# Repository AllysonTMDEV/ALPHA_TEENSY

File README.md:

# AFC - Alpha Flight Controller (Teensy 4.1)

## Visao Geral

Controlador de navegacao desenvolvido pela **Alpha Subsea** para ROVs e drones subaquaticos, baseado na plataforma **Teensy 4.1** (ARM Cortex-M7 @ 600MHz).

### Caracteristicas Principais:
- **MCU:** Teensy 4.1 (600MHz, 1MB RAM)
- **Sensores:** IMU (ICM-42688-P), Magnetometro (LIS3MDL), Barometro (BMP390), Profundidade (MS5837-30BA)
- **PWM:** 16 canais via PCA9685 (8 thrusters + 4 servos)
- **Comunicacao:** Serial 1Mbps com Raspberry Pi
- **ADC:** ADS1115 16-bit para monitoramento de tensao/corrente

## Estrutura de Arquivos

```
AFC_CICLO DESENVOLVIMENTO.html    # Ciclo de desenvolvimento (40% completo)
AFC_TEENSY_PCB_DOCUMENTACAO.md    # Documentacao tecnica completa
BOM_AFC_TEENSY_LCSC.csv           # Lista de materiais com codigos LCSC
Gerber_*.zip                       # Arquivos Gerber para fabricacao
PCB_*.json                         # PCB EasyEDA
PCB_*.kicad_pcb                    # PCB KiCad
SCH_*.json                         # Esquematico EasyEDA
Schematic_*.pdf                    # Esquematico PDF
Sheet_1_*.schdoc                   # Esquematico Altium (para KiCad)
*.png                              # Screenshots de validacao
```

## Status do Projeto

| Fase | Progresso | Status |
|------|-----------|--------|
| 1. Plan | 100% | Concluido |
| 2. Code | 100% | Firmware + Esquematico prontos |
| 3. Build | 100% | Gerbers prontos para fabricacao |
| 4. Test | 0% | Pendente |
| 5. Homologation | 0% | Pendente |

**Progresso Geral: 42%**

## BOM - Lista de Materiais

Total de **63 componentes** com codigos LCSC para montagem SMD.

### Componentes Principais:
| Componente | Modelo | LCSC |
|------------|--------|------|
| IMU 6-DoF | ICM-42688-P | C1850418 |
| Magnetometro | LIS3MDL | C478483 |
| Barometro | BMP390 | C9900016584 |
| PWM Driver | PCA9685PW | C2678753 |
| ADC 16-bit | ADS1115 | C37593 |
| Buck Converter | MP1584EN | C15051 |
| Power Monitor | INA226 | C49851 |

**Custo estimado:** ~$50-70 USD (sem Teensy e MS5837)

## Como Fabricar

1. **Fabricacao da PCB:**
   - Utilizar o arquivo `Gerber_*.zip` para fabricacao
   - BOM disponivel em `BOM_AFC_TEENSY_LCSC.csv`

2. **Importar no KiCad 9.0:**
   - `File` -> `Import Project...` -> `Altium Designer`
   - Selecionar `Sheet_1_*.schdoc`

## Firmware

Firmware desenvolvido em PlatformIO com as seguintes features:
- Loop de controle a 400Hz
- PID com anti-windup
- Mixer para 8 thrusters (BlueROV2 Heavy)
- Protocolo binario com CRC16
- Telemetria a 50Hz

## Documentacao

- [Documentacao Tecnica](AFC_TEENSY_PCB_DOCUMENTACAO.md)
- [Ciclo de Desenvolvimento](AFC_CICLO%20DESENVOLVIMENTO.html)
- [BOM LCSC](BOM_AFC_TEENSY_LCSC.csv)

## Equipe

**Alpha Subsea** - Tecnologia Submarina  
Desenvolvido por **Arbor Gestao**

---

*Ultima atualizacao: Janeiro 2026*

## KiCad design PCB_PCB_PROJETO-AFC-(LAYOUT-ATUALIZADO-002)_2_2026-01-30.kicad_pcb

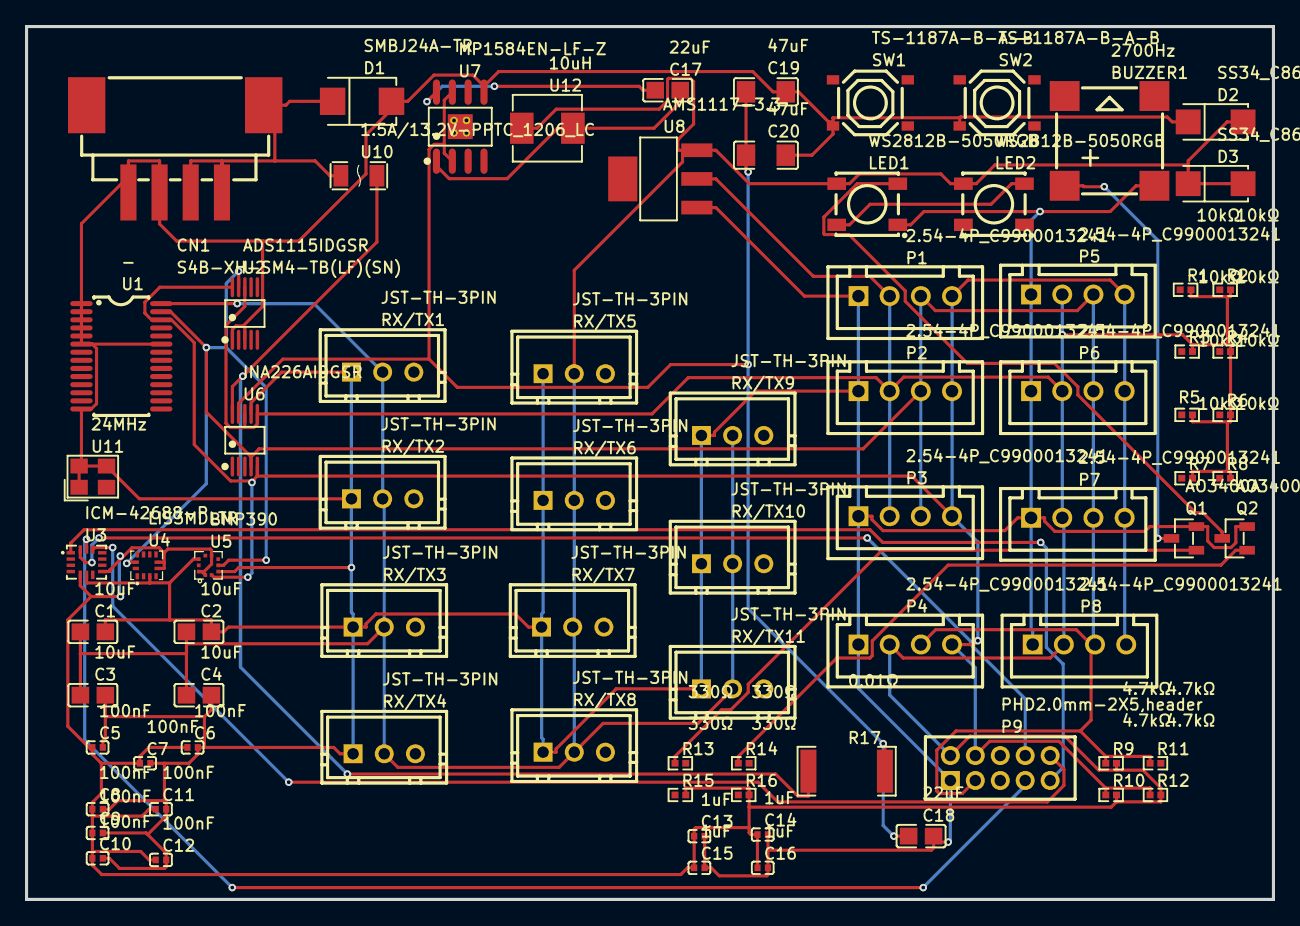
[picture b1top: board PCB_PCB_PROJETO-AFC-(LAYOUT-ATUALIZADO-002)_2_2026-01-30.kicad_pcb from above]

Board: 2 copper layers, 100.0 x 70.0 mm, 79 parts (0 on the bottom side), 19 nets.

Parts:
BUZZER1: 2700Hz; BUZ-SMD_4P-L8.5-W8.5-P8.50-BR
C1, C2, C3, C4: 10uF; C0805
C5, C6, C7, C8, C9, C10, C11, C12: 100nF; C0402
C13, C14, C15, C16: 1uF; C0402
C17, C18: 22uF; C0805
C19, C20: 47uF; C1206
CN1: S4B-XH-SM4-TB(LF)(SN); CONN-SMD_S4B-XH-SM4-TB-LF-SN
D1: SMBJ24A-TR; SMB_L4.6-W3.6-LS5.3-RD
D2, D3: SS34_C8678; SMA_L4.3-W2.6-LS5.2-RD
LED1, LED2: WS2812B-5050RGB; LED-SMD_4P-L5.0-W5.0-BR_WS2812B-5050RGB
P1, P2, P3, P4, P5, P6, P7, P8: 2.54-4P_C9900013241; CONN-TH_B4B-XH-A-BK-LF-SN
P9: PHD2.0mm-2X5,header; CONN-TH_10P-P2.00_PHD2.0MM-2X5
Q1, Q2: AO3400A; SOT-23-3_L2.9-W1.3-P1.90-LS2.4-BR
R1, R2, R3, R4, R5, R6, R7, R8: 10kΩ; R0402
R9, R10, R11, R12: 4.7kΩ; R0402
R13, R14, R15, R16: 330Ω; R0402
R17: 0.01Ω; R2512
RX/TX1, RX/TX2, RX/TX3, RX/TX4, RX/TX5, RX/TX6, RX/TX7, RX/TX8, RX/TX9, RX/TX10, RX/TX11: JST-TH-3PIN; CONN-TH_3P-P2.50_B3B-XH-A-BK-LF-SN
SW1, SW2: TS-1187A-B-A-B; SW-SMD_4P-L5.1-W5.1-P3.70-LS6.5-TL_H1.5
U1: -; TSSOP-28_L9.7-W4.4-P0.65-LS6.4-TL
U2: ADS1115IDGSR; MSOP-10_L3.0-W3.0-P0.50-LS5.0-BL
U3: ICM-42688-P; LGA-14_L3.0-W2.5-P0.50-TL
U4: LIS3MDLTR; LGA-12_L2.0-W2.0-P0.50-BL
U5: BMP390; LGA-10_L2.0-W2.0-P0.50-BL
U6: INA226AIDGSR; MSOP-10_L3.0-W3.0-P0.50-LS5.0-BL
U7: MP1584EN-LF-Z; SOIC-8_L5.0-W4.0-P1.27-LS6.0-BL-EP2.0
U8: AMS1117-3.3; SOT-223-3_L6.5-W3.4-P2.30-LS7.0-BR
U10: 1.5A/13.2V-PPTC_1206_LC; F1206
U11: 24MHz; CRYSTAL-SMD_4P-L3.2-W2.5-BL
U12: 10uH; IND-SMD_L5.4-W5.2

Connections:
3V3: C5.1, C6.1, C7.1, C8.1, C9.1, C10.1, C11.1, C12.1, C13.1, C14.1, C15.1, C16.1, P1.2, P2.2, P3.2, P4.2, P5.2, P6.2, P7.2, P8.2, P9.2, R1.2, R2.2, R3.2, R4.2, R5.2, R6.2, R7.2, R8.2, R9.2, R10.2, R12.2, R15.2, R16.2, U2.8, U3.5, U3.8, U4.5, U4.6, U5.1, U5.6, U5.10, U6.6, U6.8, U8.2
5V: C1.1, C2.1, C3.1, C4.1, D2.2, D3.1, D3.2, LED1.3, LED2.3, RX/TX1.2, RX/TX2.2, RX/TX3.2, RX/TX4.2, RX/TX5.2, RX/TX6.2, RX/TX7.2, RX/TX8.2, RX/TX9.2, RX/TX10.2, RX/TX11.2, U1.28, U8.3, U12.2
BUZZER: BUZZER1.1, Q1.3
BUZZER_CTRL: Q1.1, R13.1
CN1_1: CN1.1, CN1.2, CN1.6, D1.1, U10.1
GND: BUZZER1.2, C1.2, C2.2, C3.2, C4.2, C5.2, C6.2, C7.2, C8.2, C9.2, C10.2, C11.2, C12.2, C13.2, C14.2, C15.2, C16.2, C18.2, C19.2, C20.2, CN1.3, CN1.4, D1.2, D2.1, LED1.1, P1.1, P2.1, P3.1, P4.1, P5.1, P6.1, P7.1, P8.1, P9.1, Q1.2, Q2.2, RX/TX1.1, RX/TX2.1, RX/TX3.1, RX/TX4.1, RX/TX5.1, RX/TX6.1, RX/TX7.1, RX/TX8.1, RX/TX9.1, RX/TX10.1, RX/TX11.1, SW1.3, SW2.3, U1.1, U1.2, U1.3, U1.4, U1.5, U1.6, U1.14, U1.23, U2.1, U2.3, U3.6, U4.3, U5.3, U5.8, U6.7, U7.5, U8.1, U11.1, U11.3, U11.4
IMU_CS: P9.10, U3.12
LED1_4: LED1.4, LED2.2
LED_CTRL: Q2.1, R14.1
LED_DATA: LED1.2, Q2.3
R17_2: C18.1, C19.1, C20.1, R17.2, U6.9, U7.2, U7.7
SCL: P1.4, P2.4, P3.4, P4.4, P5.4, P6.4, P7.4, P8.4, P9.4, R10.1, R12.1, U1.26, U2.10, U5.2, U6.5
SDA: P1.3, P2.3, P3.3, P4.3, P5.3, P6.3, P7.3, P8.3, P9.3, R9.1, R11.1, U1.27, U2.9, U4.11, U5.4, U6.4
SPI_CLK: P9.7, U3.13
SPI_MISO: P9.9, U3.1
SPI_MOSI: P9.8, U3.14
U7_1: C17.2, U7.1, U12.1
U7_8: C17.1, U7.8
U10_2: R17.1, U6.10, U10.2

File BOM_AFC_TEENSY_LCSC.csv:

Referencia,Quantidade,Valor/Part Number,Descricao,Footprint,LCSC,Tipo JLCPCB
========== ICs PRINCIPAIS ==========
U1,1,PCA9685PW 118,PWM Driver 16ch I2C,TSSOP-28,C2678753,Extended Part
U2,1,ADS1115IDGSR,ADC 16-bit 4ch I2C,MSOP-10,C37593,Extended Part
U3,1,ICM-42688-P,IMU 6-axis Accel/Gyro,LGA-14,C1850418,Extended Part
U4,1,LIS3MDLTR,Magnetometro 3-axis I2C,LGA-12,C478483,Extended Part
U5,1,BMP390,Barometro/Altimetro I2C,LGA-10,C9900016584,Extended Part
U6,1,INA226AIDGSR,Monitor Corrente/Tensao I2C,MSOP-10,C49851,Extended Part
U7,1,MP1584EN-LF-Z,Buck Converter 3A,SOIC-8 EP,C15051,Extended Part
U8,1,AMS1117-3.3,LDO Regulador 3.3V 1A,SOT-223,C6186,Basic Part
U10,1,PPTC 1.5A/13.2V,Fusivel Resetavel,1206,C9900007450,Extended Part
U11,1,7325-2400A1210-03,Crystal 24MHz,SMD 3225,C17701336,Extended Part
========== DIODOS ==========
D1,1,SMBJ24A-TR,TVS Diodo 24V,SMB,C133668,Extended Part
D2,1,SS34,Schottky Diodo 3A 40V,SMA,C8678,Basic Part
D3,1,SS34,Schottky Diodo 3A 40V,SMA,C8678,Basic Part
========== TRANSISTORES ==========
Q1,1,AO3400A,MOSFET N-CH 30V 5.7A,SOT-23,C20917,Basic Part
Q2,1,AO3400A,MOSFET N-CH 30V 5.7A,SOT-23,C20917,Basic Part
========== RESISTORES ==========
R1,1,10kΩ,Resistor SMD,0402,C25744,Basic Part
R2,1,10kΩ,Resistor SMD,0402,C25744,Basic Part
R3,1,10kΩ,Resistor SMD,0402,C25744,Basic Part
R4,1,10kΩ,Resistor SMD,0402,C25744,Basic Part
R5,1,10kΩ,Resistor SMD,0402,C25744,Basic Part
R6,1,10kΩ,Resistor SMD,0402,C25744,Basic Part
R7,1,10kΩ,Resistor SMD,0402,C25744,Basic Part
R8,1,10kΩ,Resistor SMD,0402,C25744,Basic Part
R9,1,4.7kΩ,Resistor SMD,0402,C25900,Basic Part
R10,1,4.7kΩ,Resistor SMD,0402,C25900,Basic Part
R11,1,4.7kΩ,Resistor SMD,0402,C25900,Basic Part
R12,1,4.7kΩ,Resistor SMD,0402,C25900,Basic Part
R13,1,330Ω,Resistor SMD,0402,C2889360,Extended Part
R14,1,330Ω,Resistor SMD,0402,C2889360,Extended Part
R15,1,330Ω,Resistor SMD,0402,C2889360,Extended Part
R16,1,330Ω,Resistor SMD,0402,C2889360,Extended Part
R17,1,0.01Ω 1W,Resistor Shunt Sense,2512,C76272,Extended Part
========== CAPACITORES ==========
C1,1,10uF 25V,Capacitor Ceramico,0805,C15850,Basic Part
C2,1,10uF 25V,Capacitor Ceramico,0805,C15850,Basic Part
C3,1,10uF 25V,Capacitor Ceramico,0805,C15850,Basic Part
C4,1,10uF 25V,Capacitor Ceramico,0805,C15850,Basic Part
C5,1,100nF 50V,Capacitor Ceramico,0402,C1525,Basic Part
C6,1,100nF 50V,Capacitor Ceramico,0402,C1525,Basic Part
C7,1,100nF 50V,Capacitor Ceramico,0402,C1525,Basic Part
C8,1,100nF 50V,Capacitor Ceramico,0402,C1525,Basic Part
C9,1,100nF 50V,Capacitor Ceramico,0402,C1525,Basic Part
C10,1,100nF 50V,Capacitor Ceramico,0402,C1525,Basic Part
C11,1,100nF 50V,Capacitor Ceramico,0402,C1525,Basic Part
C12,1,100nF 50V,Capacitor Ceramico,0402,C1525,Basic Part
C13,1,1uF 16V,Capacitor Ceramico,0402,C52923,Basic Part
C14,1,1uF 16V,Capacitor Ceramico,0402,C52923,Basic Part
C15,1,1uF 16V,Capacitor Ceramico,0402,C52923,Basic Part
C16,1,1uF 16V,Capacitor Ceramico,0402,C52923,Basic Part
C17,1,22uF 25V,Capacitor Ceramico,0805,C45783,Basic Part
C18,1,22uF 25V,Capacitor Ceramico,0805,C45783,Basic Part
C19,1,47uF 10V,Capacitor Ceramico,1206,C5448950,Extended Part
C20,1,47uF 10V,Capacitor Ceramico,1206,C5448950,Extended Part
========== LEDs e BUZZER ==========
LED1,1,WS2812B-5050RGB,LED RGB Enderecavel,5050,C2838584,Extended Part
LED2,1,WS2812B-5050RGB,LED RGB Enderecavel,5050,C2838584,Extended Part
BUZZER1,1,MLT-8530,Buzzer 2700Hz,SMD 8.5x8.5,C94599,Extended Part
========== CONECTORES ==========
CN1,1,S4B-XH-SM4-TB(LF)(SN),Conector JST XH 4P SMD,XH-4P SMD,C5306499,Extended Part
P9,1,PHD2.0mm-2X5,Header 2x5 2mm,THT,C49123,Extended Part

========================================
RESUMO PARA PEDIDO JLCPCB (ATUALIZADO)
========================================

BASIC PARTS (estoque JLCPCB - sem taxa extra):
LCSC,Qtd,Componente
C6186,1,AMS1117-3.3 LDO
C8678,2,SS34 Schottky
C20917,2,AO3400A MOSFET
C25744,8,10kΩ 0402
C25900,4,4.7kΩ 0402
C15850,4,10uF 0805
C1525,8,100nF 0402
C52923,4,1uF 0402
C45783,2,22uF 0805

EXTENDED PARTS (taxa extra ~$3 por tipo):
LCSC,Qtd,Componente
C2678753,1,PCA9685PW PWM Driver
C37593,1,ADS1115 ADC
C1850418,1,ICM-42688-P IMU
C478483,1,LIS3MDLTR Magnetometro
C9900016584,1,BMP390 Barometro
C49851,1,INA226 Power Monitor
C15051,1,MP1584EN Buck
C9900007450,1,PPTC Fusivel
C17701336,1,Crystal 24MHz
C133668,1,SMBJ24A TVS
C2889360,4,330Ω 0402
C76272,1,0.01Ω Shunt
C5448950,2,47uF 1206
C2838584,2,WS2812B LED RGB
C94599,1,MLT-8530 Buzzer
C5306499,1,JST XH 4P
C49123,1,Header 2x5

========================================
COMPONENTES NAO LCSC (comprar separado)
========================================
TEENSY 4.1,1,Microcontrolador ARM Cortex-M7 600MHz,PJRC Store ou Aliexpress

========================================
TOTAL DE COMPONENTES: 63 unidades
========================================
- ICs: 11
- Diodos: 3
- Transistores: 2
- Resistores: 17
- Capacitores: 20
- LEDs: 2
- Buzzer: 1
- Conectores: 2
- Teensy: 1 (separado)

========================================
ESTIMATIVA DE CUSTOS (USD)
========================================
Basic Parts (35 unid): ~$1.50
Extended Parts (28 unid): ~$25-30
Taxa Extended (17 tipos x $3): ~$51
Teensy 4.1: ~$30
PCB (5 unidades): ~$5-10

TOTAL APROXIMADO: ~$115-125 para 1 placa montada

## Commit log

2026-01-30 AFC Teensy 4.1 PCB - Versao 1.0 Completa - DRC 0 erros, BOM LCSC 63 componentes, Firmware pronto
2026-01-30 correcao de caracteres
